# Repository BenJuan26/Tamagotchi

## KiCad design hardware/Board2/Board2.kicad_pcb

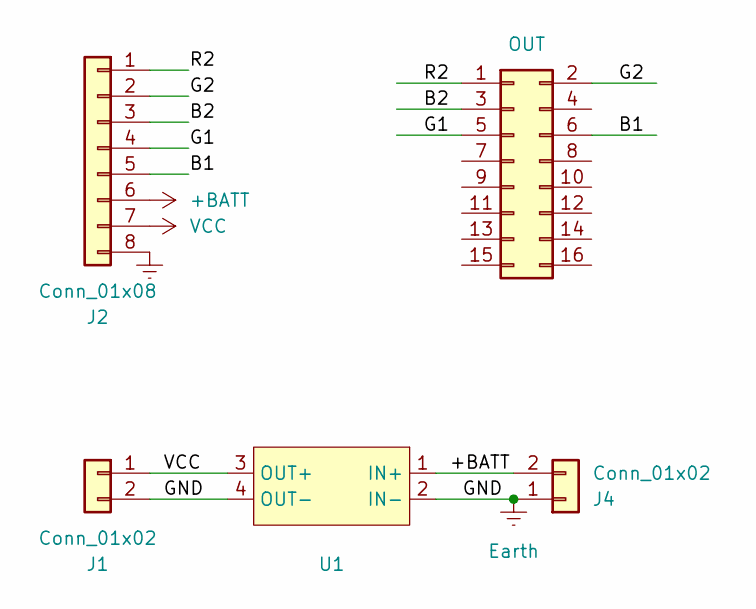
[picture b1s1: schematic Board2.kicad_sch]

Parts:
J1: Conn_01x02; JST_VH_B2PS-VH_1x02_P3.96mm_Horizontal
J2: Conn_01x08; JST_PH_S8B-PH-K_1x08_P2.00mm_Horizontal
J3: OUT; PinSocket_2x08_P2.54mm_Vertical
J4: Conn_01x02; AMASS_XT60-M_1x02_P7.20mm_Vertical
U1: LM2596-based Buck Converter

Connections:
+BATT: J2.6, J4.2, U1.1 (IN+)
/B1: J2.5, J3.6
/B2: J2.3, J3.3
/G1: J2.4, J3.5
/G2: J2.2, J3.2
/R2: J2.1, J3.1
Earth: J1.2, J2.8, J4.1, U1.2 (IN-), U1.4 (OUT-)
VCC: J1.1, J2.7, U1.3 (OUT+)

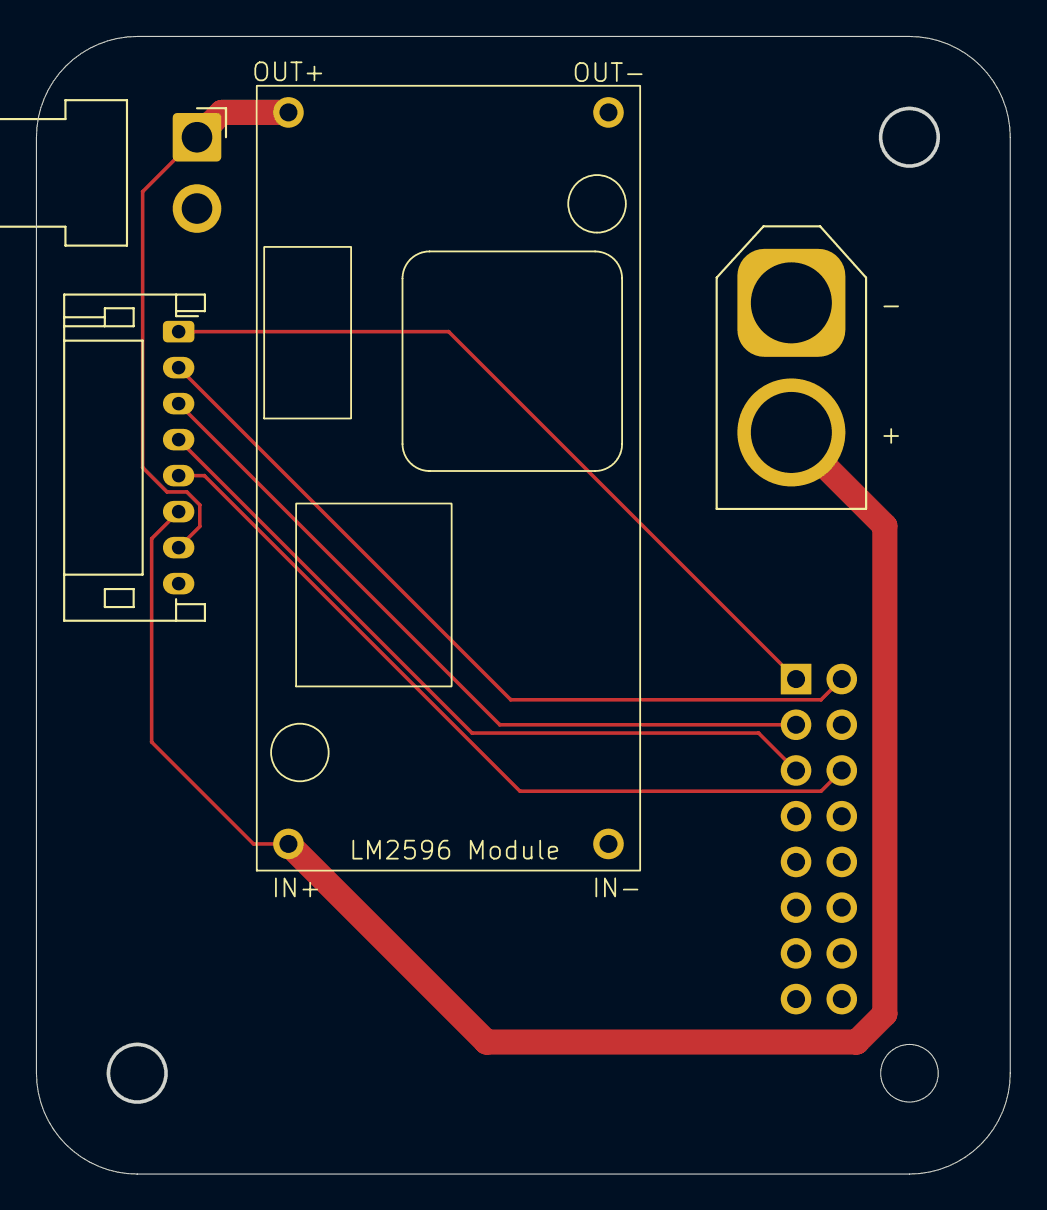
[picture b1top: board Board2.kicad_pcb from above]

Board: 2 copper layers, 54.0 x 63.1 mm, 5 parts (1 on the bottom side), 8 nets.

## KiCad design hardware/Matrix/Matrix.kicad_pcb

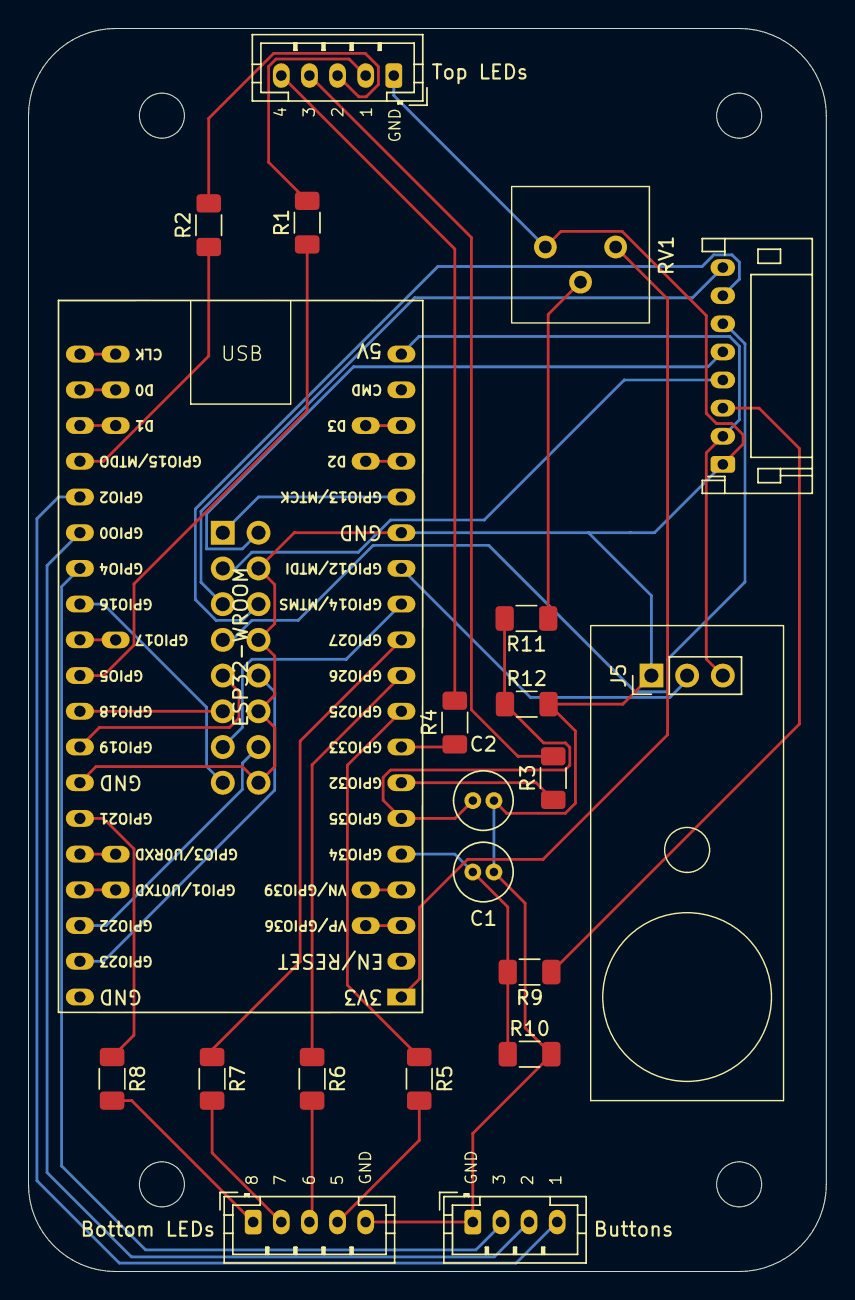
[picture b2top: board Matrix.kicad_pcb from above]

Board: 2 copper layers, 56.7 x 88.4 mm, 32 parts (1 on the bottom side), 49 nets.

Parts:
C1, C2: 100uF; C_Radial_D4.0mm_H5.0mm_P1.50mm
J1: IN; PinSocket_2x08_P2.54mm_Vertical
J3: Power and Data; JST_PH_S8B-PH-K_1x08_P2.00mm_Horizontal
J5: Buzzer; Passive_Buzzer_PCB
J6, J10, J11, J12, J13, J14, J15, J16, J17, J18: Conn_01x01; Single_Pad_2.54mm
J7: Top LEDs; JST_PH_B5B-PH-K_1x05_P2.00mm_Vertical
J8: Bottom LEDs; JST_PH_B5B-PH-K_1x05_P2.00mm_Vertical
J9: Buttons; JST_PH_B4B-PH-K_1x04_P2.00mm_Vertical
R1, R2, R3, R4, R5, R6, R7, R8: R_US; R_1206_3216Metric_Pad1.30x1.75mm_HandSolder
R9, R11: 10K; R_1206_3216Metric_Pad1.30x1.75mm_HandSolder
R10: 3.9K; R_1206_3216Metric_Pad1.30x1.75mm_HandSolder
R12: 39K; R_1206_3216Metric_Pad1.30x1.75mm_HandSolder
RV1: 10K; Potentiometer_Vertical
U1: ESP32-WROOM; ESP32-KIDSROBOT

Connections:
+3V3: RV1.1, U1.1 (3V3)
+BATT: J3.3, R9.1
/B1: J1.3, J3.4
/B2: J1.7, J3.6
/G1: J1.2, J3.5
/G2: J1.6, J3.7
/LED1: J7.2, R1.2
/LED2: J7.3, R2.2
/LED3: J7.4, R3.2
/LED4: J7.5, R4.2
/LED5: J8.4, R5.2
/LED6: J8.3, R6.2
/LED7: J8.2, R7.2
/LED8: J8.1, R8.2
/P0: J9.3, U1.25 (GPIO0/BOOT/ADC2_CH1)
/P1: J11.1, U1.35 (U0TXD/GPIO1)
/P2: J9.4, U1.24 (ADC2_CH2/GPIO2)
/P3: J10.1, U1.34 (U0RXD/GPIO3)
/P4: J9.2, U1.26 (ADC2_CH0/GPIO4)
/P5: R1.1, U1.29 (GPIO5)
/P6: J18.1, U1.20 (SD_CLK/GPIO6)
/P7: J17.1, U1.21 (SD_DATA0/GPIO7)
/P8: J16.1, U1.22 (SD_DATA1/GPIO8)
/P9: J13.1, U1.16 (SD_DATA2/GPIO9)
/P10: J14.1, U1.17 (SD_DATA3/GPIO10)
/P12: J5.2, U1.13 (MTDI/GPIO12/ADC2_CH5)
/P13: J1.1, U1.15 (MTCK/GPIO13/ADC2_CH4)
/P14: J1.13, U1.12 (MTMS/GPIO14/ADC2_CH6)
/P15: R2.1, U1.23 (MTDO/GPIO15/ADC2_CH3)
/P16: J1.15, U1.27 (GPIO16)
/P17: J15.1, U1.28 (GPIO17)
/P18: J1.11, U1.30 (GPIO18)
/P19: J1.9, U1.31 (GPIO19)
/P21: R8.1, U1.33 (GPIO21)
/P22: J1.14, U1.36 (GPIO22)
/P23: J1.10, U1.37 (GPIO23)
/P25: R5.1, U1.9 (DAC_1/ADC2_CH8/GPIO25)
/P26: R6.1, U1.10 (DAC_2/ADC2_CH9/GPIO26)
/P27: R7.1, U1.11 (ADC2_CH7/GPIO27)
/P32: R3.1, U1.7 (32K_XP/GPIO32/ADC1_CH4)
/P33: R4.1, U1.8 (32K_XN/GPIO33/ADC1_CH5)
/P34: C1.1, R9.2, R10.1, U1.5 (VDET_1/GPIO34/ADC1_CH6)
/P35: C2.1, R11.2, R12.1, U1.6 (VDET_2/GPIO35/ADC1_CH7)
/P36: J6.1, U1.3 (SENSOR_VP/GPIO36/ADC1_CH0)
/P39: J12.1, U1.4 (SENSOR_VN/GPIO39/ADC1_CH3)
/R2: J1.5, J3.8
Earth: C1.2, C2.2, J1.4, J1.8, J1.12, J1.16, J3.1, J5.1, J7.1, J8.5, J9.1, R10.2, R12.2, RV1.3, U1.14 (GND), U1.32 (GND), U1.38 (GND)
unnamed: R11.1, RV1.2
VCC: J3.2, J5.3, U1.19 (5V)

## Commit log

2024-09-07 Committing before I break something
2024-09-07 Jk, it was already broken
2024-09-07 Don't need Px in Arduino
2024-09-09 Sort of working?
2024-09-11 Working (without icons) on ESP32
2024-09-12 OTA and LEDs working except the last one
2025-04-02 Add hardware
2025-04-05 BG color
2025-04-06 ISR for Matrix update
2025-04-24 Almost done with boards
2025-04-24 Maybe done boards?
